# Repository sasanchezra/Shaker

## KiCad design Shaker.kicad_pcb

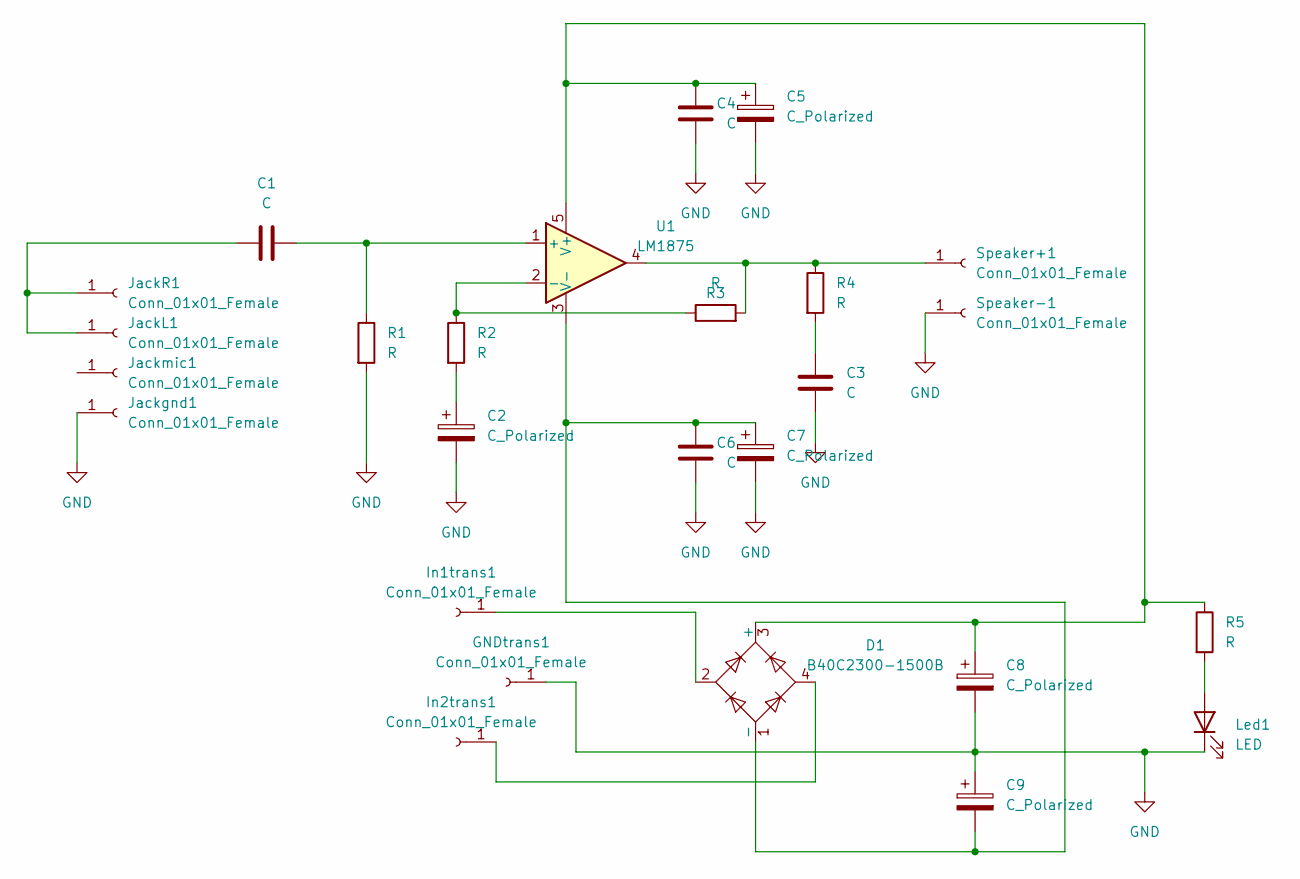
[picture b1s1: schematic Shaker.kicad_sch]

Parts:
C1, C3, C4, C6: C; C_Disc_D3.4mm_W2.1mm_P2.50mm
C2, C5, C7, C8, C9: C_Polarized; CP_Radial_D10.0mm_P3.80mm
D1: B40C2300-1500B; Diode_Bridge_Vishay_KBU
GNDtrans1: Conn_01x01_Female; SolderWire-0.5sqmm_1x01_D0.9mm_OD2.3mm
In1trans1, In2trans1: Conn_01x01_Female; SolderWire-0.5sqmm_1x01_D0.9mm_OD2.3mm
JackL1: Conn_01x01_Female; SolderWire-0.5sqmm_1x01_D0.9mm_OD2.3mm
JackR1: Conn_01x01_Female; SolderWire-0.5sqmm_1x01_D0.9mm_OD2.3mm
Jackgnd1: Conn_01x01_Female; SolderWire-0.5sqmm_1x01_D0.9mm_OD2.3mm
Jackmic1: Conn_01x01_Female; SolderWire-0.5sqmm_1x01_D0.9mm_OD2.3mm
Led1: LED; LED_D2.0mm_W4.0mm_H2.8mm_FlatTop
R1, R2, R3, R4, R5: R; R_Axial_DIN0414_L11.9mm_D4.5mm_P20.32mm_Horizontal
Speaker+1: Conn_01x01_Female; SolderWire-0.5sqmm_1x01_D0.9mm_OD2.3mm
Speaker-1: Conn_01x01_Female; SolderWire-0.5sqmm_1x01_D0.9mm_OD2.3mm
U1: LM1875; TO-220F-5_P3.4x2.06mm_StaggerOdd_Lead1.86mm_Vertical

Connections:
GND: C2.2, C3.1, C4.1, C5.2, C6.1, C7.2, C8.2, C9.1, GNDtrans1.1, Jackgnd1.1, Led1.1 (K), R1.2, Speaker-1.1
unnamed: C1.1, JackL1.1, JackR1.1
unnamed: C1.2, R1.1, U1.1 (+)
unnamed: C2.1, R2.2
unnamed: C3.2, R4.2
unnamed: C4.2, C5.1, C8.1, D1.3 (+), R5.1, U1.5 (V+)
unnamed: C6.2, C7.1, C9.2, D1.1 (-), U1.3 (V-)
unnamed: D1.2, In1trans1.1
unnamed: D1.4, In2trans1.1
unnamed: R2.1, R3.1, U1.2 (-)
unnamed: R3.2, R4.1, Speaker+1.1, U1.4
unnamed: Led1.2 (A), R5.2

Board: 2 copper layers, 26 parts (0 on the bottom side), 12 nets, no tracks yet.

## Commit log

2022-03-05 Esquemático finalizado
2022-03-05 huellas creadas
